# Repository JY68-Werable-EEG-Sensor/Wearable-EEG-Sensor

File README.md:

# Wearable-EEG-Sensor
## Overview
Git Repository for JY68 Wearable EEG Sensor Capstone Project
Use this repository for:
1. Diagrams
2. PCB files
    1. Schematics
    2. Layouts
3. Application codebase
4. 3D CAD files
## Description
This Project is a novel, wearable, single-channel EEG device and it's associated display application.
## Team
Albert, Chris, Connor, Peak, Taher

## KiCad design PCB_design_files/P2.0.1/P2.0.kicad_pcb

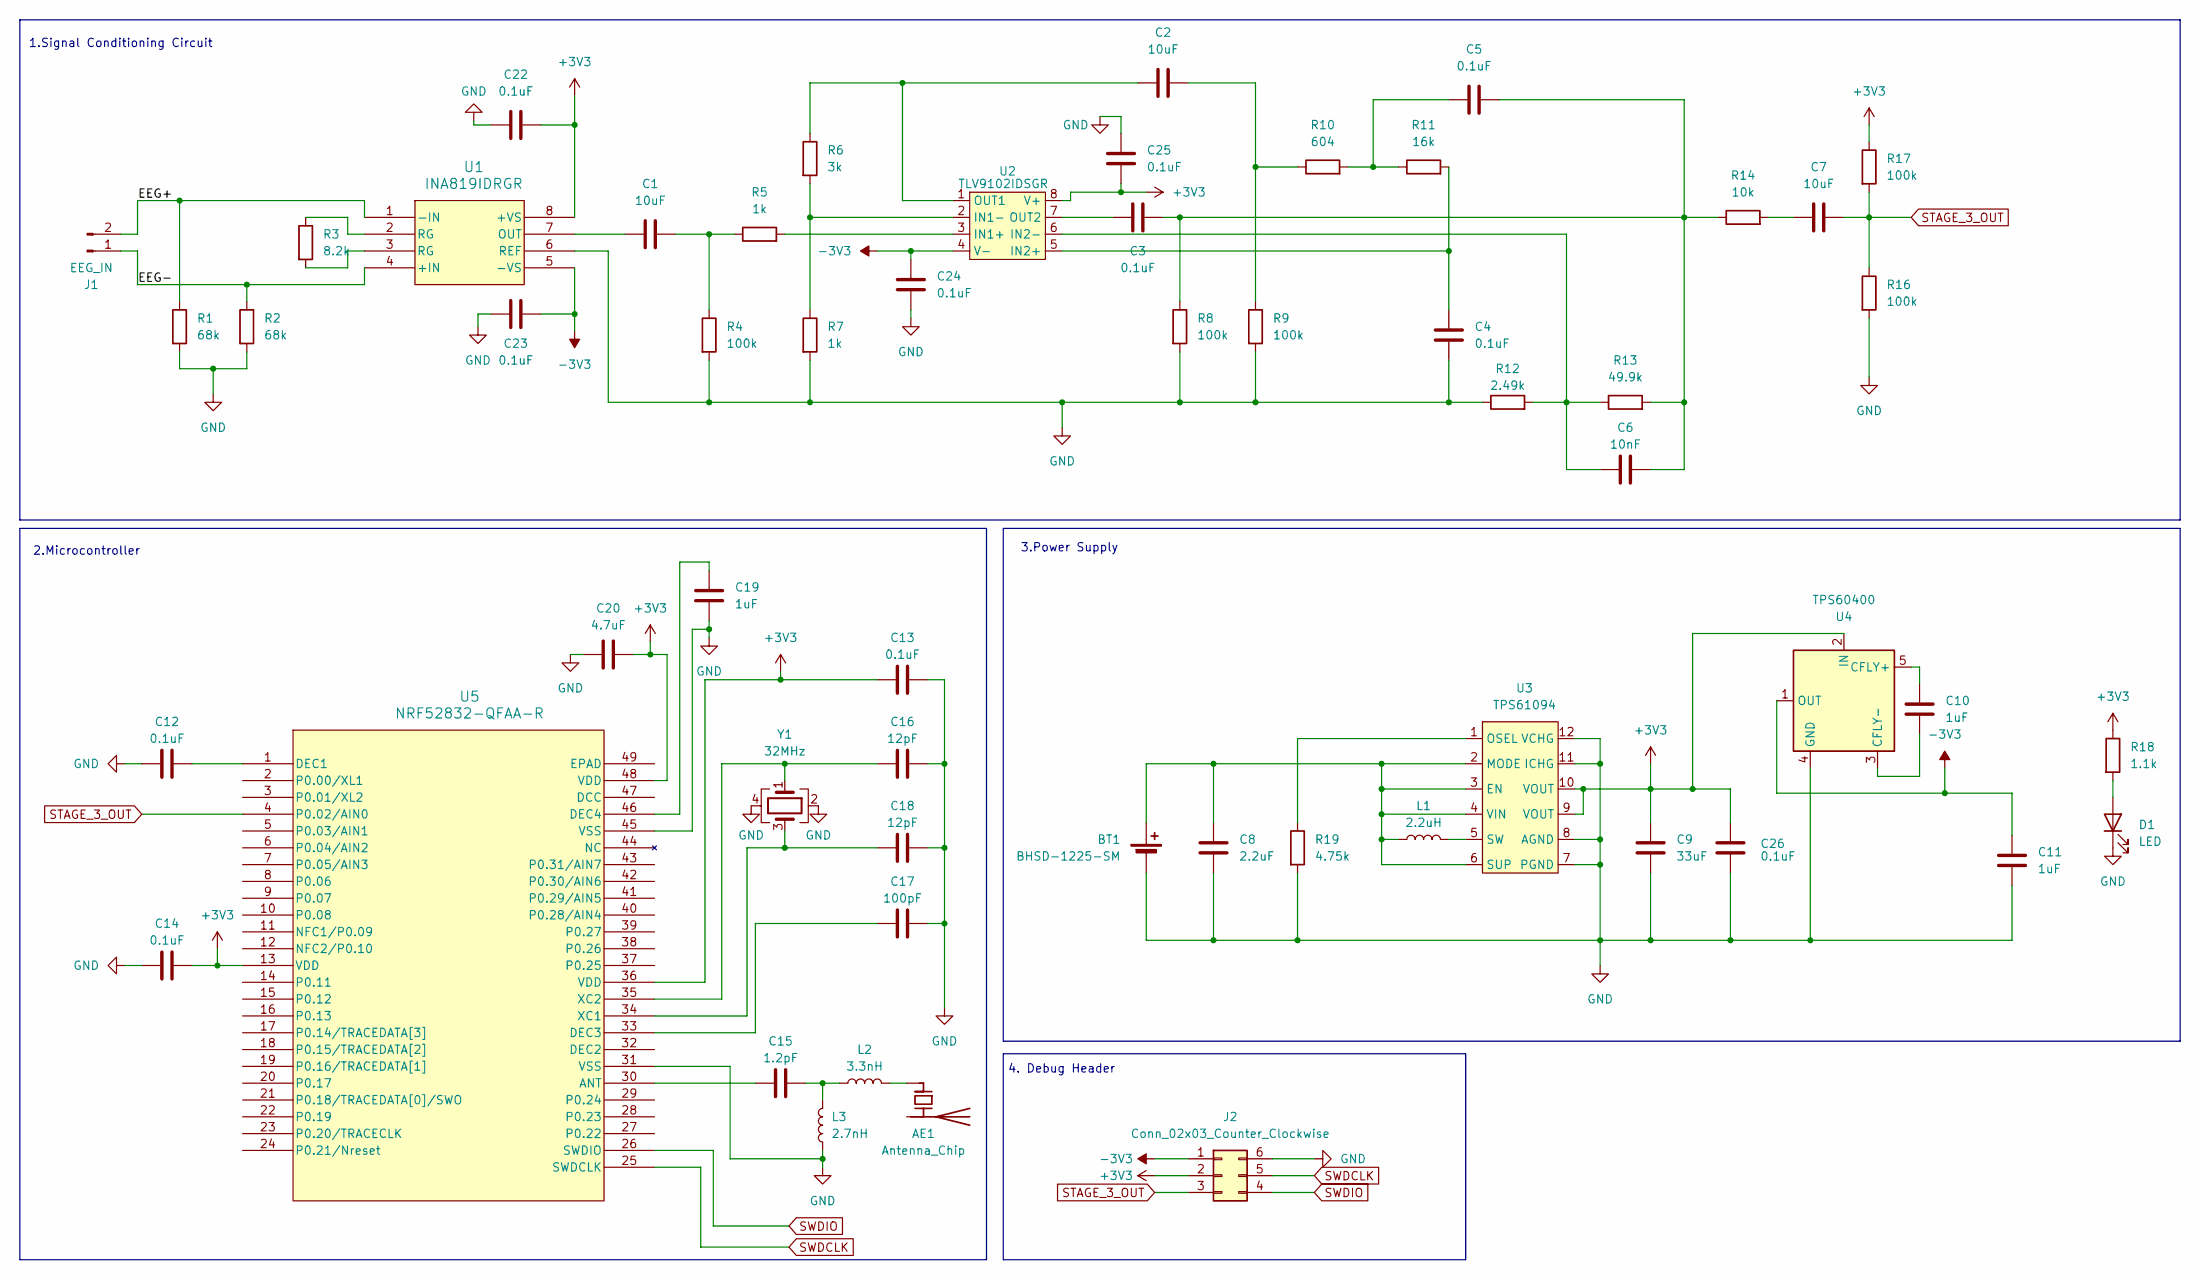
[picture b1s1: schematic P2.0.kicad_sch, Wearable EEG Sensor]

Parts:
AE1: Antenna_Chip; XDCR_2450AT18B100E; Part Number 2450AT18B0100001E
BT1: BHSD-1225-SM; PinSocket_1x02_P2.54mm_Vertical; Part Number n/a
C1, C2, C7: 10uF; C_0402_1005Metric; Part Number CC0402MPX5R5BB106
C3, C4, C5, C12, C13, C14, C22, C23, C24, C25, C26: 0.1uF; C_0402_1005Metric; Part Number C1005X7R1C104K050BC
C6: 10nF; C_0402_1005Metric; Part Number CGA2B2X7R1E103K050BA
C8: 2.2uF; C_0402_1005Metric; Part Number C1005X5R0J225K050BC
C9: 33uF; C_0805_2012Metric; Part Number C2012X5R0J336M125AC
C10, C11: 1uF; C_0402_1005Metric; Part Number C1005X5R1E105K050BC
C15: 1.2pF; C_0402_1005Metric; Part Number CC0402BRNPO9BN1R2
C16, C18: 12pF; C_0402_1005Metric; Part Number CGA2B2C0G1H120J050BA
C17: 100pF; C_0402_1005Metric; Part Number CGA2B2C0G1H101J050BA
C19: 1uF; C_0603_1608Metric; Part Number C1608X5R1A105K080AC
C20: 4.7uF; C_0603_1608Metric; Part Number C1608X5R1E475K080AC
D1: LED; LED_0603_1608Metric; Part Number 150060VS75000
J1: EEG_IN; PinHeader_1x02_P2.54mm_Vertical; Part Number n/a
J2: Conn_02x03_Counter_Clockwise; AMPHENOL_20021121-00006C4LF; Part Number 20021121-00006C4LF
L1: 2.2uH; L_0603_1608Metric; Part Number MBKK1608T2R2M
L2: 3.3nH; L_0402_1005Metric; Part Number MLG1005S3N3BT000
L3: 2.7nH; L_0402_1005Metric; Part Number MLG1005S2N7ST000
R1, R2: 68k; R_0402_1005Metric; Part Number RMCF0402FT68K0
R3: 8.2k; R_0402_1005Metric; Part Number RMCF0402FT8K20
R4, R8, R9, R16, R17: 100k; R_0402_1005Metric; Part Number RMCF0402FT100K
R5, R7: 1k; R_0402_1005Metric; Part Number RMCF0402FT1K00
R6: 3k; R_0402_1005Metric; Part Number RMCF0402FT3K00
R10: 604; R_0402_1005Metric; Part Number RMCF0402FT604R
R11: 16k; R_0402_1005Metric; Part Number RMCF0402FT16K0
R12: 2.49k; R_0402_1005Metric; Part Number RMCF0402FT2K49
R13: 49.9k; R_0402_1005Metric; Part Number RMCF0402FT49K9
R14: 10k; R_0402_1005Metric; Part Number RMCF0402FT10K0
R18: 1.1k; R_0402_1005Metric; Part Number RMCF0402FT1K10
R19: 4.75k; R_0402_1005Metric; Part Number RMCF0402FT4K75
U1: INA819IDRGR; WSON-8-1EP_3x3mm_P0.5mm_EP1.45x2.4mm; Part Number INA819IDRGR
U2: TLV9102IDSGR; WSON-8-1EP_2x2mm_P0.5mm_EP0.9x1.6mm; Part Number TLV9102IDSGR
U3: TPS61094; WSON-12-1EP_3x2mm_P0.5mm_EP1x2.65; Part Number TPS61094
U4: TPS60400; SOT-23-5; Part Number TPS60400DBV
U5: NRF52832-QFAA-R; QFN-48_NOR; Part Number NRF52832-QFAA-R
Y1: 32MHz; XTAL_ECS-320-8-37CKM; Part Number ECS-320-8-37CKM

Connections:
+3V3: C9.2, C13.2, C14.1, C20.1, C22.2, C25.2, C26.2, J2.2, R17.1, R18.1, U1.8 (+VS), U2.8 (V+), U3.9 (VOUT), U3.10 (VOUT), U4.2 (IN), U5.13 (VDD), U5.36 (VDD), U5.48 (VDD)
-3V3: C11.2, C23.2, C24.2, J2.1, U1.5 (-VS), U1.9, U2.4 (V-), U2.9, U4.1 (OUT)
/EEG+: J1.2, R1.1, U1.1 (-IN)
/EEG-: J1.1, R2.1, U1.4 (+IN)
GND: BT1.2 (-), C4.1, C8.1, C9.1, C11.1, C12.2, C13.1, C14.2, C16.1, C17.1, C18.1, C19.2, C20.2, C22.1, C23.1, C24.1, C25.1, C26.1, D1.1 (K), J2.6, L3.1, R1.2, R2.2, R4.2, R7.2, R8.2, R9.2, R12.1, R16.2, R19.2, U1.6 (REF), U3.7 (PGND), U3.8 (AGND), U3.11 (ICHG), U3.12 (VCHG), U3.13, U4.4 (GND), U5.31 (VSS), U5.45 (VSS), U5.49 (EPAD), Y1.2, Y1.4
unnamed: AE1.1 (FEED), L2.2
unnamed: BT1.1 (+), C8.2, L1.1, U3.2 (MODE), U3.3 (EN), U3.4 (VIN), U3.6 (SUP)
unnamed: C1.2, R4.1, R5.1
unnamed: C2.2, R9.1, R10.1
unnamed: C3.2, C5.2, C6.2, R8.1, R13.2, R14.1
unnamed: C5.1, R10.2, R11.1
unnamed: C7.1, R14.2
unnamed: C15.1, L2.1, L3.2
unnamed: D1.2 (A), R18.2
unnamed: R3.1, U1.2 (RG)
unnamed: R3.2, U1.3 (RG)
unnamed: C1.1, U1.7 (OUT)
unnamed: R5.2, U2.3 (IN1+)
unnamed: R6.2, R7.1, U2.2 (IN1-)
unnamed: C4.2, R11.2, U2.5 (IN2+)
unnamed: C6.1, R12.2, R13.1, U2.6 (IN2-)
unnamed: C2.1, R6.1, U2.1 (OUT1)
unnamed: C3.1, U2.7 (OUT2)
unnamed: R19.1, U3.1 (OSEL)
unnamed: L1.2, U3.5 (SW)
unnamed: C10.1, U4.5 (CFLY+)
unnamed: C10.2, U4.3 (CFLY-)
unnamed: C15.2, U5.30 (ANT)
unnamed: C12.1, U5.1 (DEC1)
unnamed: C17.2, U5.33 (DEC3)
unnamed: C19.1, U5.46 (DEC4)
unnamed: C18.2, U5.34 (XC1), Y1.3
unnamed: C16.2, U5.35 (XC2), Y1.1
STAGE_3_OUT: C7.2, J2.3, R16.1, R17.2, U5.4 (P0.02/AIN0)
SWDCLK: J2.5, U5.25 (SWDCLK)
SWDIO: J2.4, U5.26 (SWDIO)

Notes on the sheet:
2.Microcontroller
4. Debug Header
3.Power Supply
1.Signal Conditioning Circuit

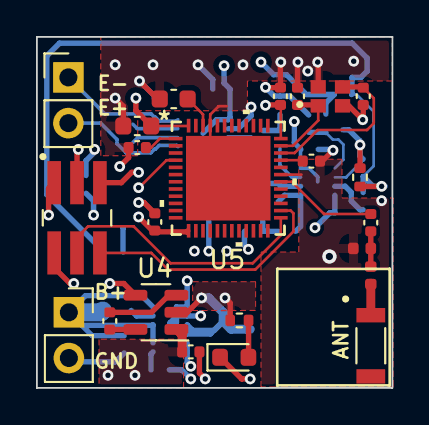
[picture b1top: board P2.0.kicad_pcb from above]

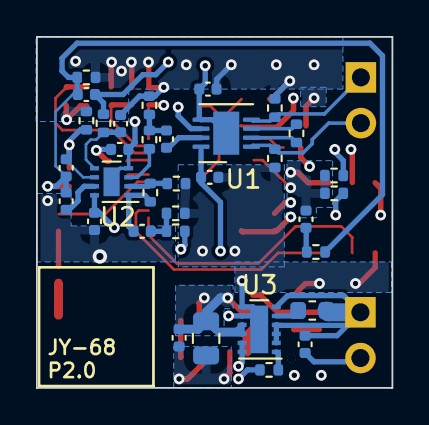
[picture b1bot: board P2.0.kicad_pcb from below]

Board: 4 copper layers, 19.8 x 19.5 mm, 57 parts (34 on the bottom side), 36 nets.

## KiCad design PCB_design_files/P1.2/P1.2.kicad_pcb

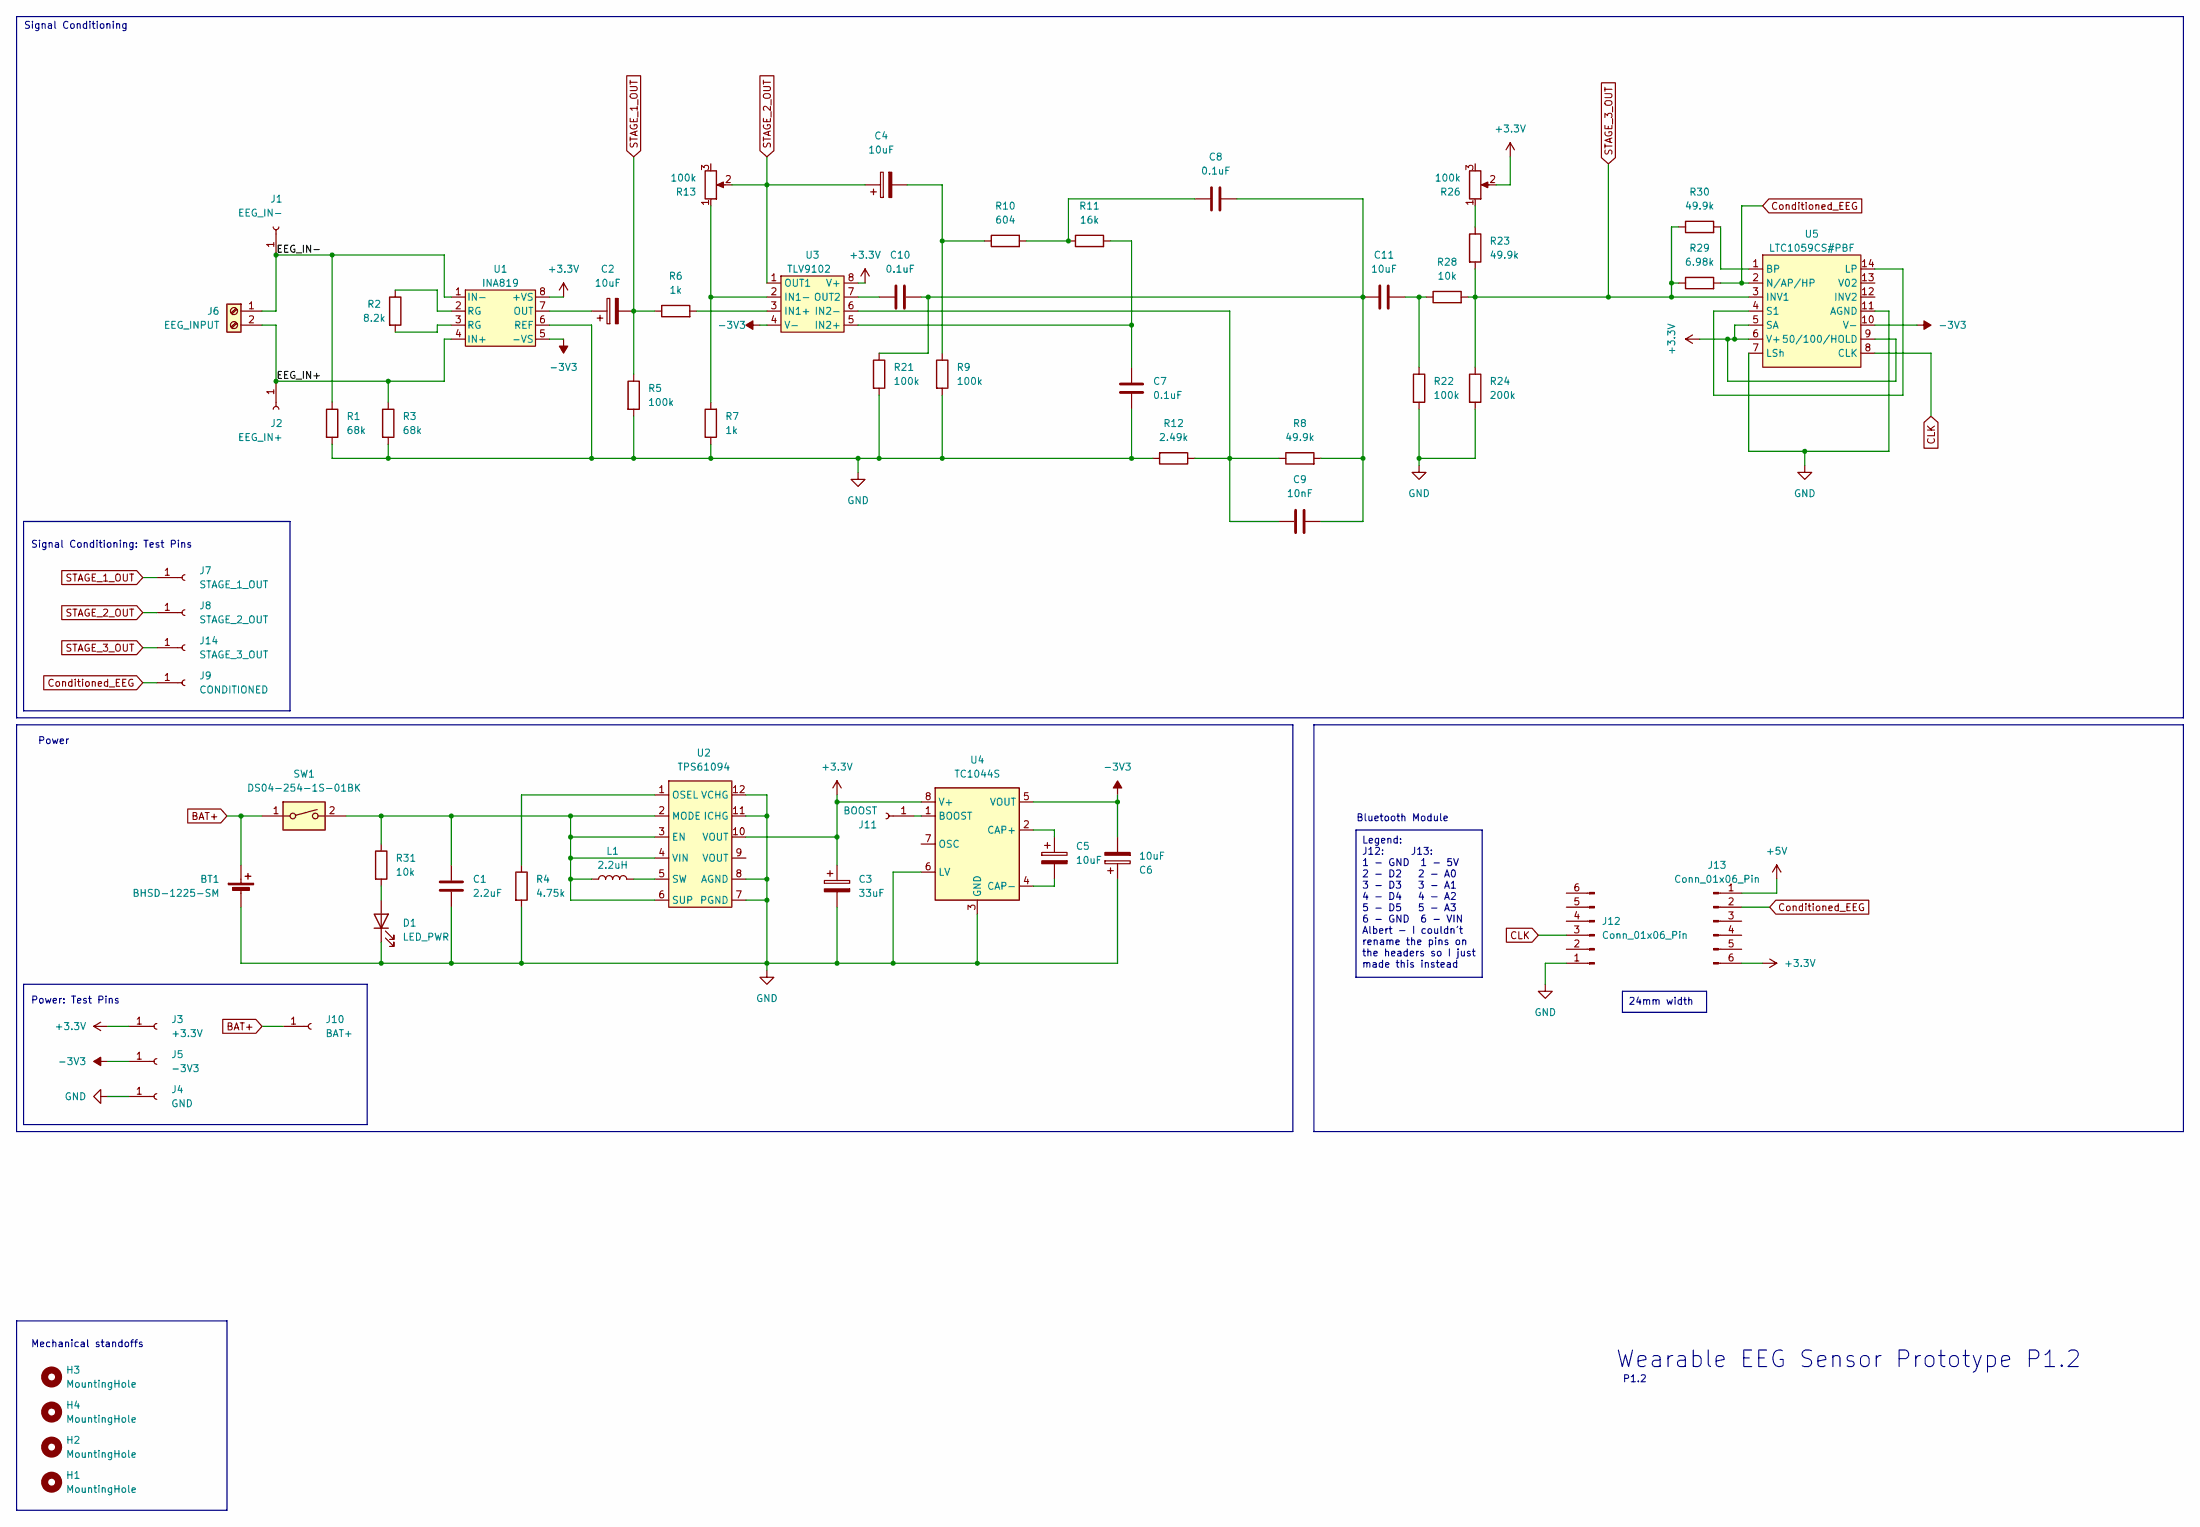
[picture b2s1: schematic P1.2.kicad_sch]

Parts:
BT1: BHSD-1225-SM; BAT_BHSD-1225-SM
C1: 2.2uF; C_Rect_L7.0mm_W4.5mm_P5.00mm
C2, C4, C5, C6, C11: 10uF; CP_Radial_D5.0mm_P2.50mm
C3: 33uF; CP_Radial_D8.0mm_P5.00mm
C7, C10: 0.1uF; C_Rect_L7.0mm_W4.5mm_P5.00mm
C8: 0.1uF; C_Rect_L7.0mm_W2.5mm_P5.00mm
C9: 10nF; C_Rect_L7.0mm_W2.5mm_P5.00mm
D1: LED_PWR; LED_D5.0mm
H1, H2, H3, H4: MountingHole; MountingHole_3.2mm_M3
J1: EEG_IN-; TestPoint_Loop_D2.50mm_Drill1.0mm
J2: EEG_IN+; TestPoint_Loop_D2.50mm_Drill1.0mm
J3: +3.3V; TestPoint_Loop_D2.50mm_Drill1.0mm
J4: GND; TestPoint_Loop_D2.50mm_Drill1.0mm
J5: -3V3; TestPoint_Loop_D2.50mm_Drill1.0mm
J6: EEG_INPUT; 282837-2_TYC
J7: STAGE_1_OUT; TestPoint_Loop_D2.50mm_Drill1.0mm
J8: STAGE_2_OUT; TestPoint_Loop_D2.50mm_Drill1.0mm
J9: CONDITIONED; TestPoint_Loop_D2.50mm_Drill1.0mm
J10: BAT+; TestPoint_Loop_D2.50mm_Drill1.0mm
J11: BOOST; TestPoint_Loop_D2.50mm_Drill1.0mm
J12, J13: Conn_01x06_Pin; PinSocket_1x06_P2.54mm_Vertical
J14: STAGE_3_OUT; TestPoint_Loop_D2.50mm_Drill1.0mm
L1: 2.2uH; INDAD1400W80L920D400
R1, R3: 68k; R_Axial_DIN0207_L6.3mm_D2.5mm_P10.16mm_Horizontal
R2: 8.2k; R_Axial_DIN0207_L6.3mm_D2.5mm_P10.16mm_Horizontal
R4: 4.75k; R_Axial_DIN0207_L6.3mm_D2.5mm_P10.16mm_Horizontal
R5, R9, R21, R22: 100k; R_Axial_DIN0207_L6.3mm_D2.5mm_P10.16mm_Horizontal
R6, R7: 1k; R_Axial_DIN0207_L6.3mm_D2.5mm_P10.16mm_Horizontal
R8, R23, R30: 49.9k; R_Axial_DIN0207_L6.3mm_D2.5mm_P10.16mm_Horizontal
R10: 604; R_Axial_DIN0207_L6.3mm_D2.5mm_P10.16mm_Horizontal
R11: 16k; R_Axial_DIN0207_L6.3mm_D2.5mm_P10.16mm_Horizontal
R12: 2.49k; R_Axial_DIN0207_L6.3mm_D2.5mm_P10.16mm_Horizontal
R13, R26: 100k; Potentiometer_Bourns_3296W_Vertical
R24: 200k; R_Axial_DIN0207_L6.3mm_D2.5mm_P10.16mm_Horizontal
R28, R31: 10k; R_Axial_DIN0207_L6.3mm_D2.5mm_P10.16mm_Horizontal
R29: 6.98k; R_Axial_DIN0207_L6.3mm_D2.5mm_P10.16mm_Horizontal
SW1: DS04-254-1S-01BK; SW_DS04-254-1S-01BK
U1: INA819; DIP-8_W7.62mm_Socket_LongPads
U2: TPS61094; WSON_94DSSR_TEX
U3: TLV9102; DIP-8_W7.62mm_Socket_LongPads
U4: TC1044S; CONN8_1-2199298-2_TEC
U5: LTC1059CS#PBF; DIP-14_W7.62mm_LongPads

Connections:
+3.3V: C3.1, J3.1, J13.6, R26.2, U1.8 (+VS), U2.10 (VOUT), U3.8 (V+), U4.8 (V+), U5.5 (SA), U5.6 (V+), U5.9 (50/100/HOLD)
+5V: J13.1
-3V3: C6.2, J5.1, U1.5 (-VS), U3.4 (V-), U4.5 (VOUT), U5.10 (V-)
/EEG_IN+: J2.1, J6.2, R3.1, U1.4 (IN+)
/EEG_IN-: J1.1, J6.1, R1.1, U1.1 (IN-)
BAT+: BT1.1 (+), J10.1, SW1.1
CLK: J12.3, U5.8 (CLK)
Conditioned_EEG: J9.1, J13.2, R29.2, U5.2 (N/AP/HP)
GND: BT1.2 (-), C1.2, C3.2, C6.1, C7.1, D1.1 (K), J4.1, J12.1, R1.2, R3.2, R4.2, R5.2, R7.1, R9.2, R12.2, R21.2, R22.2, R24.2, U1.6 (REF), U2.7 (PGND), U2.8 (AGND), U2.11 (ICHG), U2.12 (VCHG), U4.3 (GND), U4.6 (LV), U5.7 (LSh), U5.11 (AGND)
unnamed: C4.2, R9.1, R10.1
unnamed: C8.2, R10.2, R11.1
unnamed: C8.1, C9.1, C10.1, C11.1, R8.2, R21.1
unnamed: C11.2, R22.1, R28.1
unnamed: D1.2 (A), R31.2
unnamed: J11.1, U4.1 (BOOST)
unnamed: R2.1, U1.2 (RG)
unnamed: R2.2, U1.3 (RG)
unnamed: R23.1, R26.1
unnamed: C2.1, U1.7 (OUT)
unnamed: C1.1, L1.1, R31.1, SW1.2, U2.2 (MODE), U2.3 (EN), U2.4 (VIN), U2.6 (SUP)
unnamed: R4.1, U2.1 (OSEL)
unnamed: L1.2, U2.5 (SW)
unnamed: R6.2, U3.3 (IN1+)
unnamed: R7.2, R13.1, U3.2 (IN1-)
unnamed: C7.2, R11.2, U3.5 (IN2+)
unnamed: C9.2, R8.1, R12.1, U3.6 (IN2-)
unnamed: C10.2, U3.7 (OUT2)
unnamed: C5.1, U4.2 (CAP+)
unnamed: C5.2, U4.4 (CAP-)
unnamed: R30.2, U5.1 (BP)
unnamed: U5.4 (S1), U5.14 (LP)
STAGE_1_OUT: C2.2, J7.1, R5.1, R6.1
STAGE_2_OUT: C4.1, J8.1, R13.2, U3.1 (OUT1)
STAGE_3_OUT: J14.1, R23.2, R24.1, R28.2, R29.1, R30.1, U5.3 (INV1)

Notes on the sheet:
24mm width
Legend: J12: J13: 1 - GND 1 - 5V 2 - D2 2 - A0 3 - D3 3 - A1 4 - D4 4 - A2 5 - D5 5 - A3 6 - GND 6 - VIN Albert - I couldn't rename the pins on the headers so I just made this instead
P1.2
Signal Conditioning: Test Pins
Power
Signal Conditioning
Power: Test Pins
Bluetooth Module
Wearable EEG Sensor Prototype P1.2
Mechanical standoffs

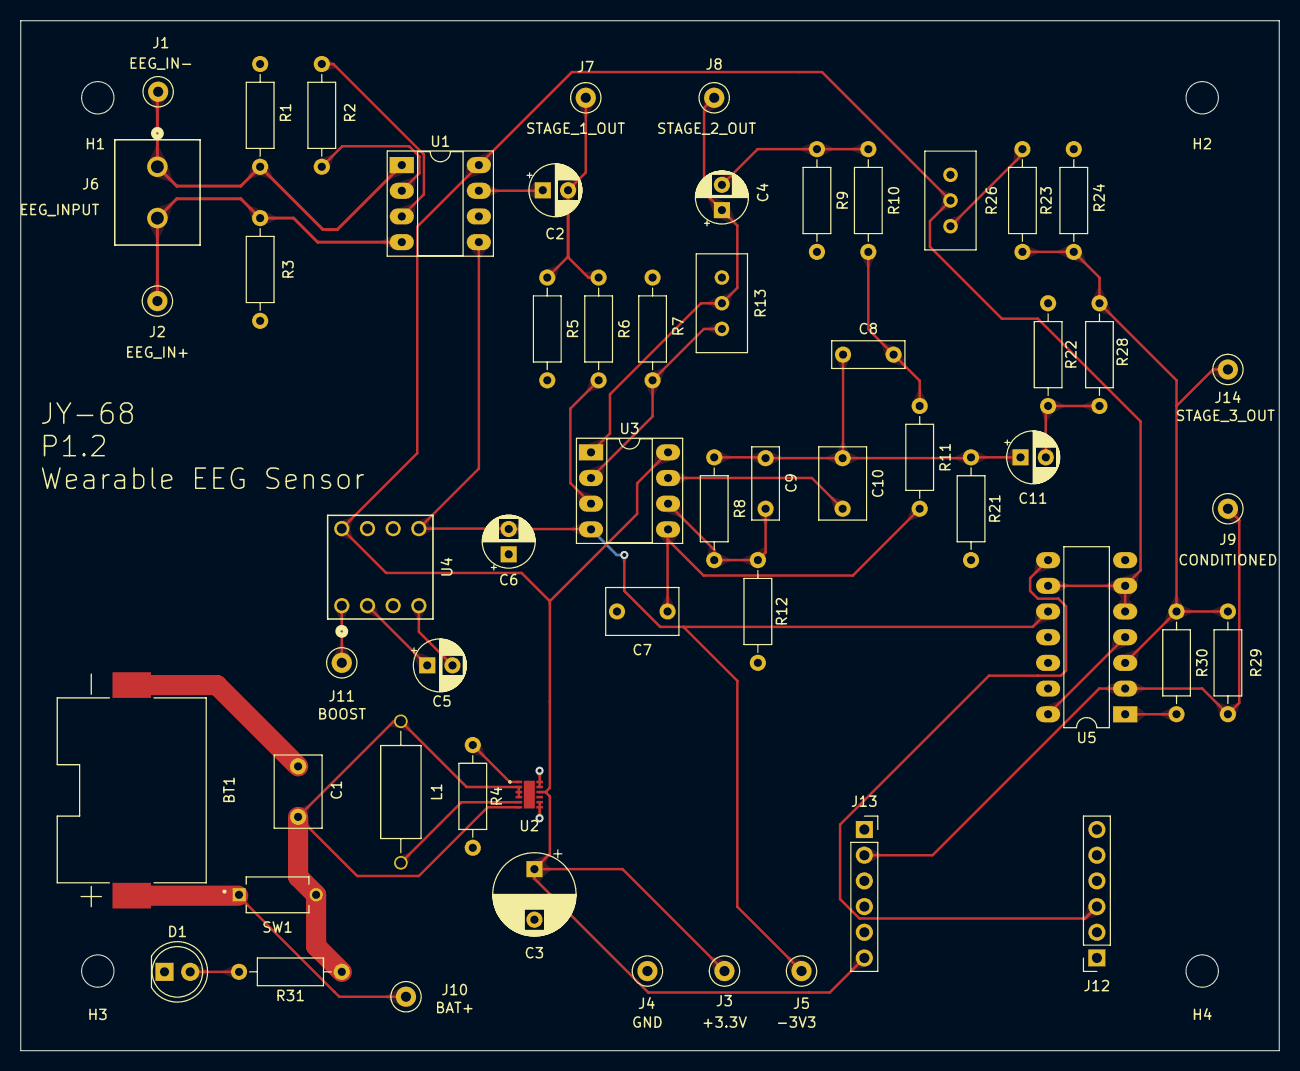
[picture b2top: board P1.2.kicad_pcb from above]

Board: 2 copper layers, 124.5 x 101.9 mm, 60 parts (0 on the bottom side), 33 nets.

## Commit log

2023-11-06 Added SystemArchitecture.drawio
2023-11-09 Uploading all KiCad stuff
2023-11-14 Push
2023-11-15 Clarified schematic topology
2023-11-15 Added some footprints to schematic
2023-11-15 removed backup files. Added note to schematic
2023-11-15 Changed passive values, moved potentiometer location, two versions with different power supply
2023-11-15 Also added new LTSpice test circuits
2023-11-16 Added a new project that takes TLV9102 as an 8-pin SOIC
2023-11-16 Created .gitignore
2023-11-16 deleted backup zips
2023-11-17 Renamed capstone_alt to P1.2
2023-11-17 Renamed directories and added a README
2023-11-17 Added footprints for existing components
2023-11-17 added some testpoints
2023-11-18 Fixed some symbols. Started PCB layout
2023-11-19 fixed some IC symbols
2023-11-20 Created PCB Layout
2023-11-23 swapped R13 and R8
2023-11-23 Resistor values should now match those purchased
2023-11-23 added lock files to gitignore
2023-11-25 created sample AWS gateway
2023-11-25 send randomized json data to s3 bucket
2023-11-29 Updated schematic based on Nov.25 lab tests
2023-11-29 Added bluetooth_architecture.drawio
2023-11-29 Wrote sample bluetooth server script
2023-11-30 Added offset
2024-01-15 Updated schematic
2024-01-16 Updated schematic based on Alberts latest changes
2024-01-16 Added footprint for power switch
2024-01-16 Minor schematic changes
2024-01-16 Updated resistor values
2024-01-17 Redesigning PCB
2024-01-17 Updated PCB layout
2024-01-17 Design review changes
2024-01-25 Added P1.2 manufacture files
2024-01-26 Started on P2.0
2024-01-27 More P2.0 schematic work
2024-01-29 Started PCB
2024-01-31 PCB layout and component footprint updates
2024-01-31 Done
2024-01-31 Increased board size
2024-02-12 Overlay
2024-02-12 Config
2024-02-12 Updated P2.0
2024-02-13 Fixed for P2.0
2024-02-26 Footprint
2024-02-29 added web display to main repo
2024-03-02 P2.0
2024-03-05 Adding backup file
2024-03-05 add theme and color to frontend
2024-03-06 Updated LED footprint
2024-03-07 Added decoupling capacitors and updated layout
2024-03-07 PCB layout updates
2024-03-07 Changed all resistor footprints to 0402
2024-03-07 Changed manufacturing and descirptions of passive comoponents
2024-03-08 Changed C19, C12 footprints
2024-03-08 Finished assignment of footprints and descriptions
2024-03-08 Some more revisions
2024-03-10 made some schematic updates
2024-03-10 Schematic updates
2024-03-11 Adding manfuacturing files
2024-03-11 Generated assembly files and rearranged manufacturing files
2024-03-11 Updated manufacturing files
2024-03-11 Added P2.0.1
2024-03-12 Design review updates
2024-03-14 Decoupling sending and sampling
2024-03-17 BLE receive update
2024-03-17 Increased size to 500
2024-03-19 Latest
2024-03-19 Guaranteed single channel sorted - sending and sampling during interrupt
2024-03-19 Updated sender and receiver so non-consecutive samples are logged
2024-03-19 Sorted
2024-03-20 Initial attempt at binary sending instead
2024-03-20 idiotic but minimal example demonstrating buffer filling and reading
2024-03-20 Character based example
2024-03-20 Verified we can send 244 bytes and corresponds to process_and_send_saadc_data trigger
2024-03-20 Tentatively sorted
2024-03-20 Tentatively sorted 2
2024-03-22 website v2 with homepage and new chart.js
2024-03-22 Added filtering to script
2024-03-24 Add media files for project submission
2024-03-28 update linechart
2024-03-29 python communicate to websocket and data is retrieve to react app
2024-03-29 add code to prevent queue from becoming too big
2024-04-07 start stop attempt
2024-04-07 Send instantly
2024-04-07 CRC implemented
2024-04-10 made history page
